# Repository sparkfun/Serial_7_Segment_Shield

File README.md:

Serial_7_Segment_Shield
=======================

The Serial 7 Segment Shield allows for easy use of the 4 digit 1" seven segment displays.

Repository Contents
-------------------

* **/hardware** - Eagle PCB layout files

Version History
---------------
* vH02 First production run
* vH01 First protoboard run.

License Information
-------------------

The hardware is released under [Creative Commons Share-alike 3.0](http://creativecommons.org/licenses/by-sa/3.0/).

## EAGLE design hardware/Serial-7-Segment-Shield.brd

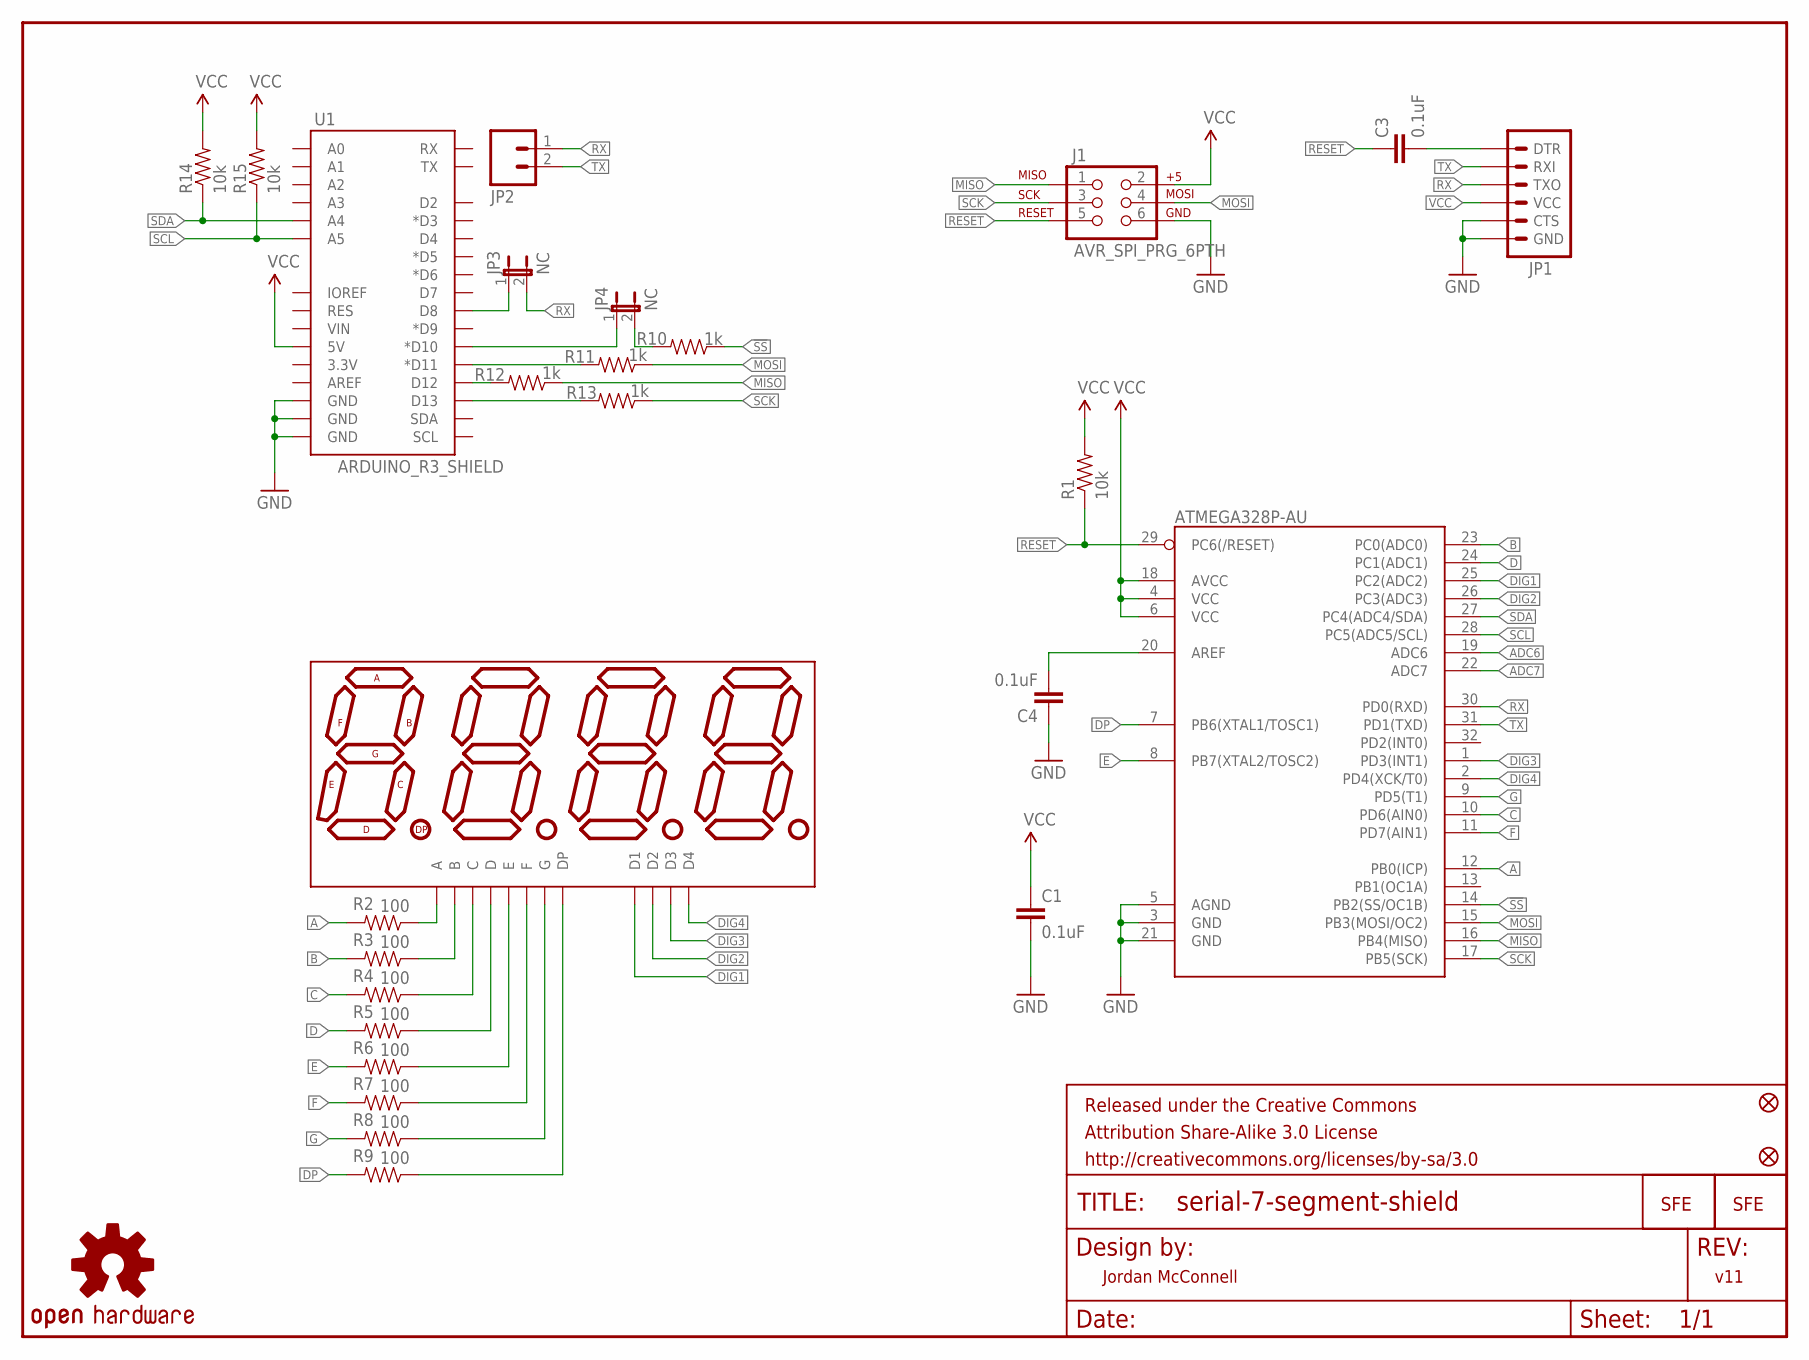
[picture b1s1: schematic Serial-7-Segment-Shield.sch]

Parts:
ATMEGA328P-AU: ATMEGA328P-AU; TQFP32-08
C1, C3, C4: 0.1uF; 0603-CAP
FID1, FID2: FIDUCIAL1X2; FIDUCIAL-1X2
FRAME1: FRAME-LETTER; CREATIVE_COMMONS
J1: AVR_SPI_PRG_6PTH; 2X3
JP1: ARDUINO_SERIAL_PROGRAMPTH; 1X06
JP2: M02PTH; 1X02
JP3, JP4: NC; SJ_2S
LOGO1, LOGO2: LOGO-SFENEW; SFE-NEW-WEBLOGO
R1, R14, R15: 10k; 0603-RES
R2, R3, R4, R5, R6, R7, R8, R9: 100; 0603-RES
R10, R11, R12, R13: 1k; 0603-RES
U1: ARDUINO_R3_SHIELD; UNO_R3_SHIELD
U$1: 7-SEGMENT-4DIGIT-COUNTERPTH; 7-SEGMENT-4DIGIT-COUNTER
U$4: OSHW-LOGOS; OSHW-LOGO-S

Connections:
!SS: ATMEGA328P-AU.14 (PB2(SS/OC1B)), R10.1
A: ATMEGA328P-AU.12 (PB0(ICP)), R2.2
ADC6: ATMEGA328P-AU.19 (ADC6)
ADC7: ATMEGA328P-AU.22 (ADC7)
B: ATMEGA328P-AU.23 (PC0(ADC0)), R3.2
C: ATMEGA328P-AU.10 (PD6(AIN0)), R4.2
D: ATMEGA328P-AU.24 (PC1(ADC1)), R5.2
DIG1: ATMEGA328P-AU.25 (PC2(ADC2)), U$1.12 (D1)
DIG2: ATMEGA328P-AU.26 (PC3(ADC3)), U$1.9 (D2)
DIG3: ATMEGA328P-AU.1 (PD3(INT1)), U$1.8 (D3)
DIG4: ATMEGA328P-AU.2 (PD4(XCK/T0)), U$1.6 (D4)
DP: ATMEGA328P-AU.7 (PB6(XTAL1/TOSC1)), R9.2
E: ATMEGA328P-AU.8 (PB7(XTAL2/TOSC2)), R6.2
F: ATMEGA328P-AU.11 (PD7(AIN1)), R7.2
G: ATMEGA328P-AU.9 (PD5(T1)), R8.2
GND: ATMEGA328P-AU.3 (GND), ATMEGA328P-AU.5 (AGND), ATMEGA328P-AU.21 (GND), C1.2, C4.1, J1.6, JP1.5 (CTS), JP1.6 (GND), U1.GND@0 (GND), U1.GND@1 (GND), U1.GND@2 (GND)
MISO: ATMEGA328P-AU.16 (PB4(MISO)), J1.1, R12.1
MOSI: ATMEGA328P-AU.15 (PB3(MOSI/OC2)), J1.4, R11.1
unnamed: ATMEGA328P-AU.20 (AREF), C4.2
unnamed: R13.2, U1.D13
unnamed: R12.2, U1.D12
unnamed: R11.2, U1.D11 (*D11)
unnamed: JP4.2, R10.2
unnamed: JP4.1, U1.D10 (*D10)
unnamed: JP3.1, U1.D8
unnamed: R2.1, U$1.11 (A)
unnamed: R3.1, U$1.7 (B)
unnamed: C3.2, JP1.1 (DTR)
unnamed: R4.1, U$1.4 (C)
unnamed: R5.1, U$1.2 (D)
unnamed: R6.1, U$1.1 (E)
unnamed: R7.1, U$1.10 (F)
unnamed: R8.1, U$1.5 (G)
unnamed: R9.1, U$1.3 (DP)
RESET: ATMEGA328P-AU.29 (PC6(/RESET)), C3.1, J1.5, R1.1
RX: ATMEGA328P-AU.30 (PD0(RXD)), JP1.3 (TXO), JP2.1, JP3.2
SCK: ATMEGA328P-AU.17 (PB5(SCK)), J1.3, R13.1
SCL: ATMEGA328P-AU.28 (PC5(ADC5/SCL)), R15.1, U1.A5
SDA: ATMEGA328P-AU.27 (PC4(ADC4/SDA)), R14.1, U1.A4
TX: ATMEGA328P-AU.31 (PD1(TXD)), JP1.2 (RXI), JP2.2
VCC: ATMEGA328P-AU.4 (VCC), ATMEGA328P-AU.6 (VCC), ATMEGA328P-AU.18 (AVCC), C1.1, J1.2, JP1.4 (VCC), R1.2, R14.2, R15.2, U1.5V

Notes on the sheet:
Jordan McConnell
v11

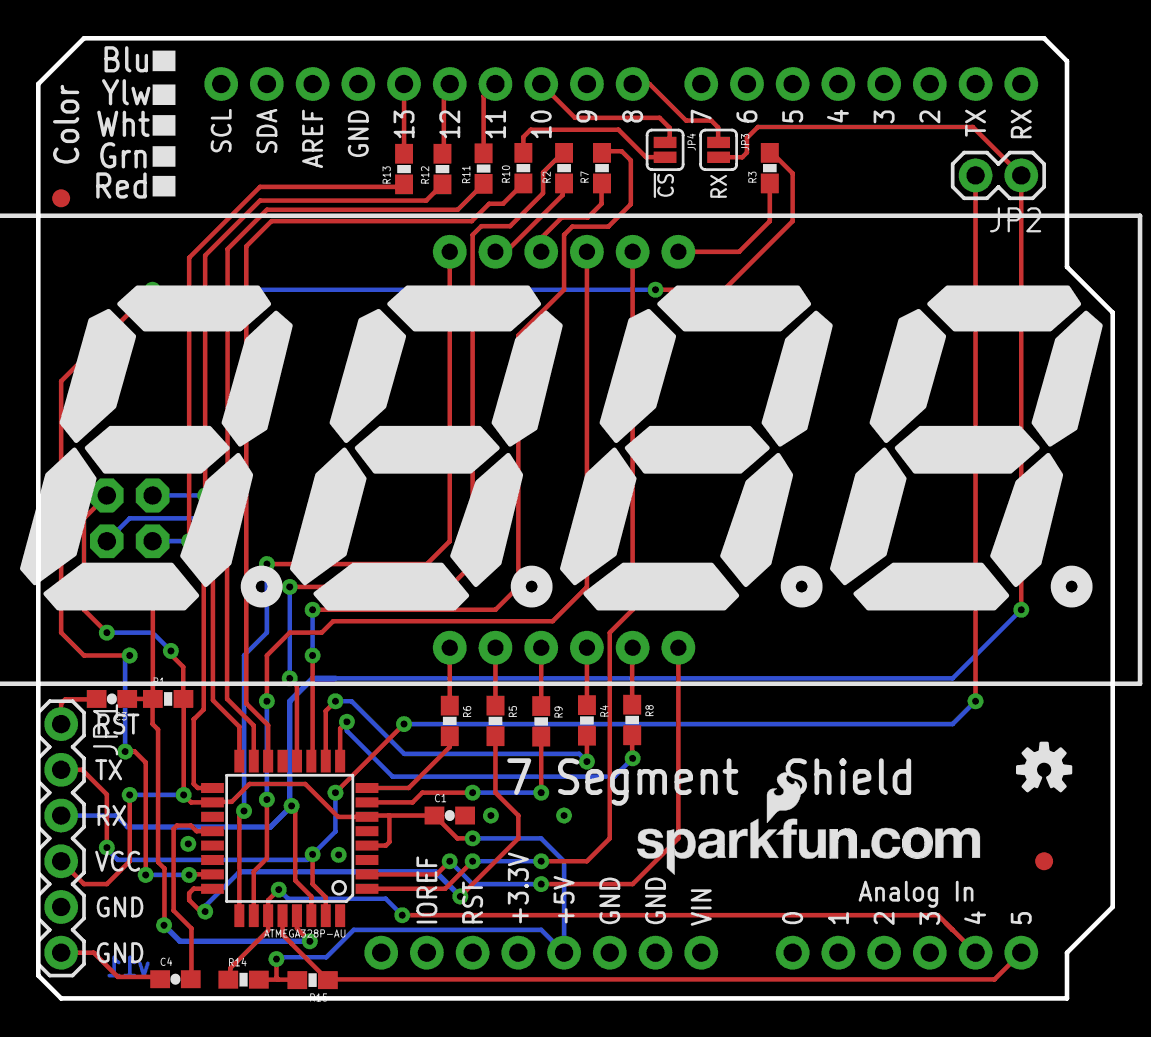
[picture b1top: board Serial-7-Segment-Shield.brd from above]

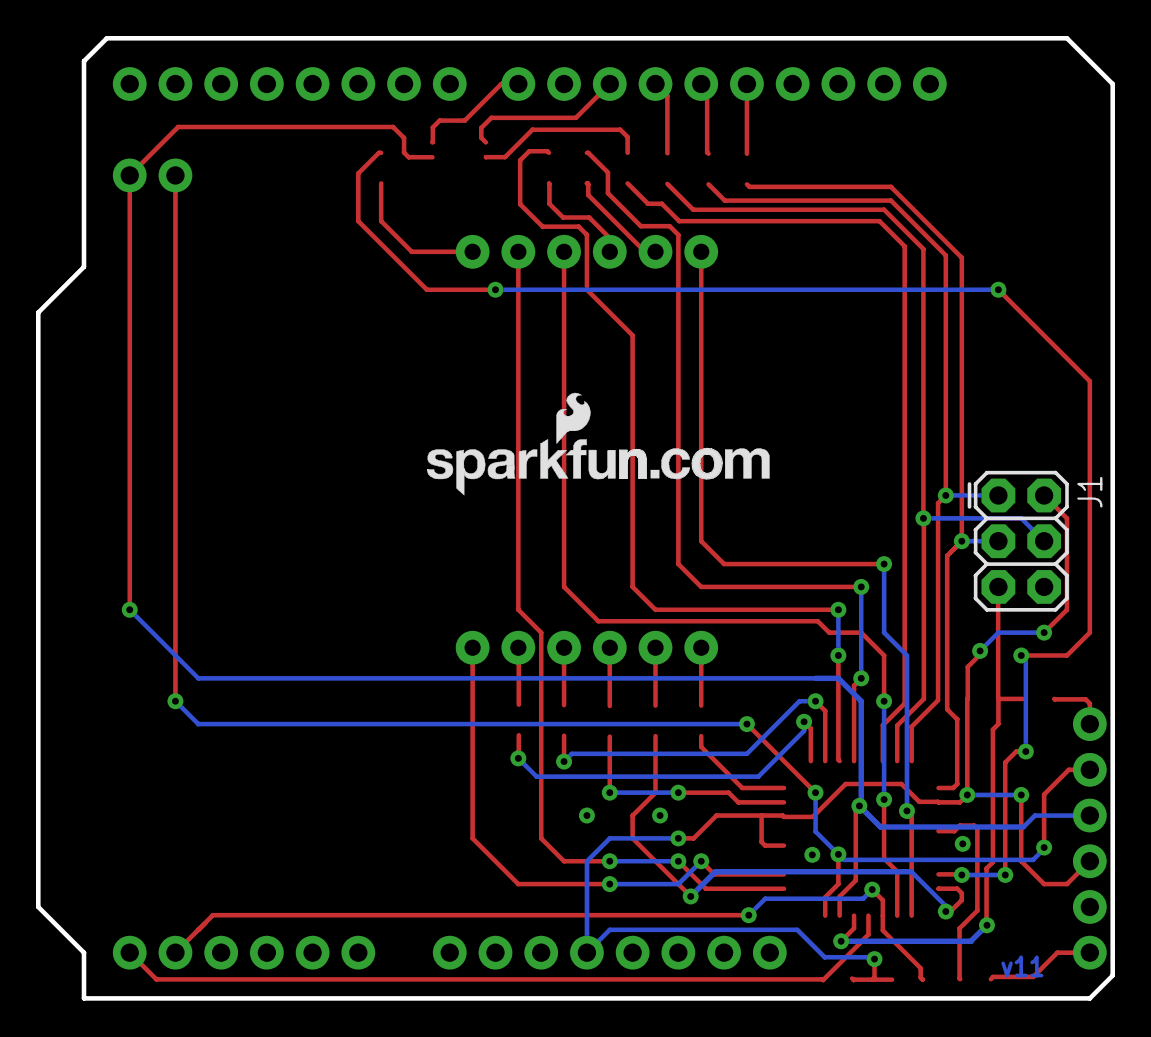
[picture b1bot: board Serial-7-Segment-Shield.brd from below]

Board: 2 copper layers, 59.7 x 53.3 mm, 32 parts (2 on the bottom side), 39 nets.

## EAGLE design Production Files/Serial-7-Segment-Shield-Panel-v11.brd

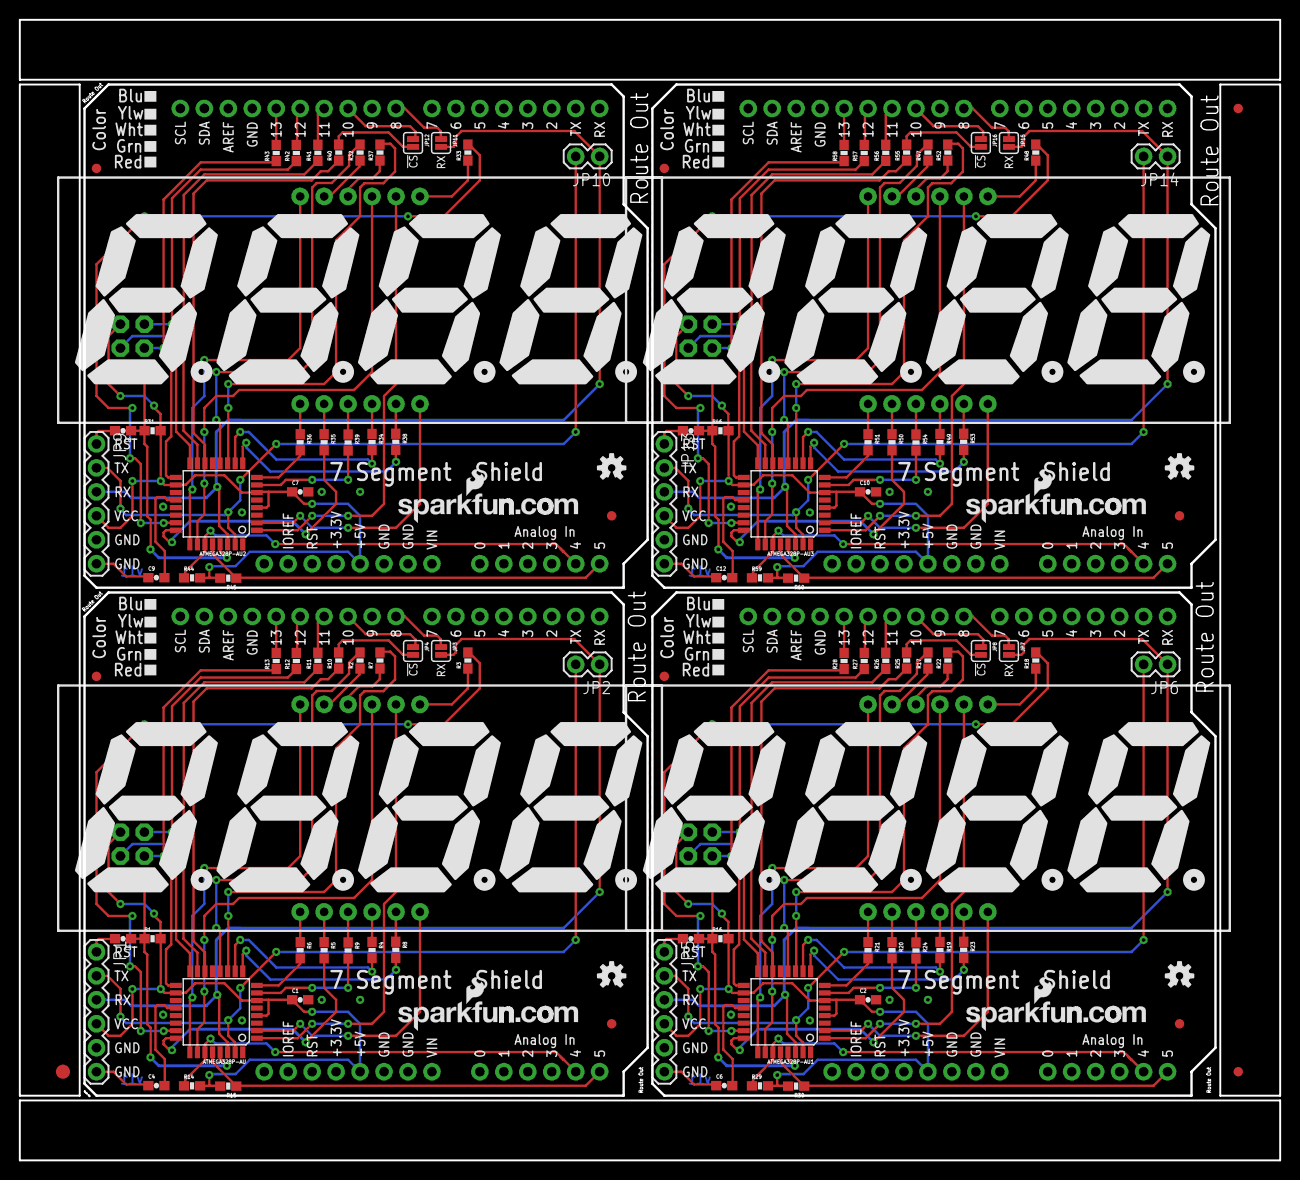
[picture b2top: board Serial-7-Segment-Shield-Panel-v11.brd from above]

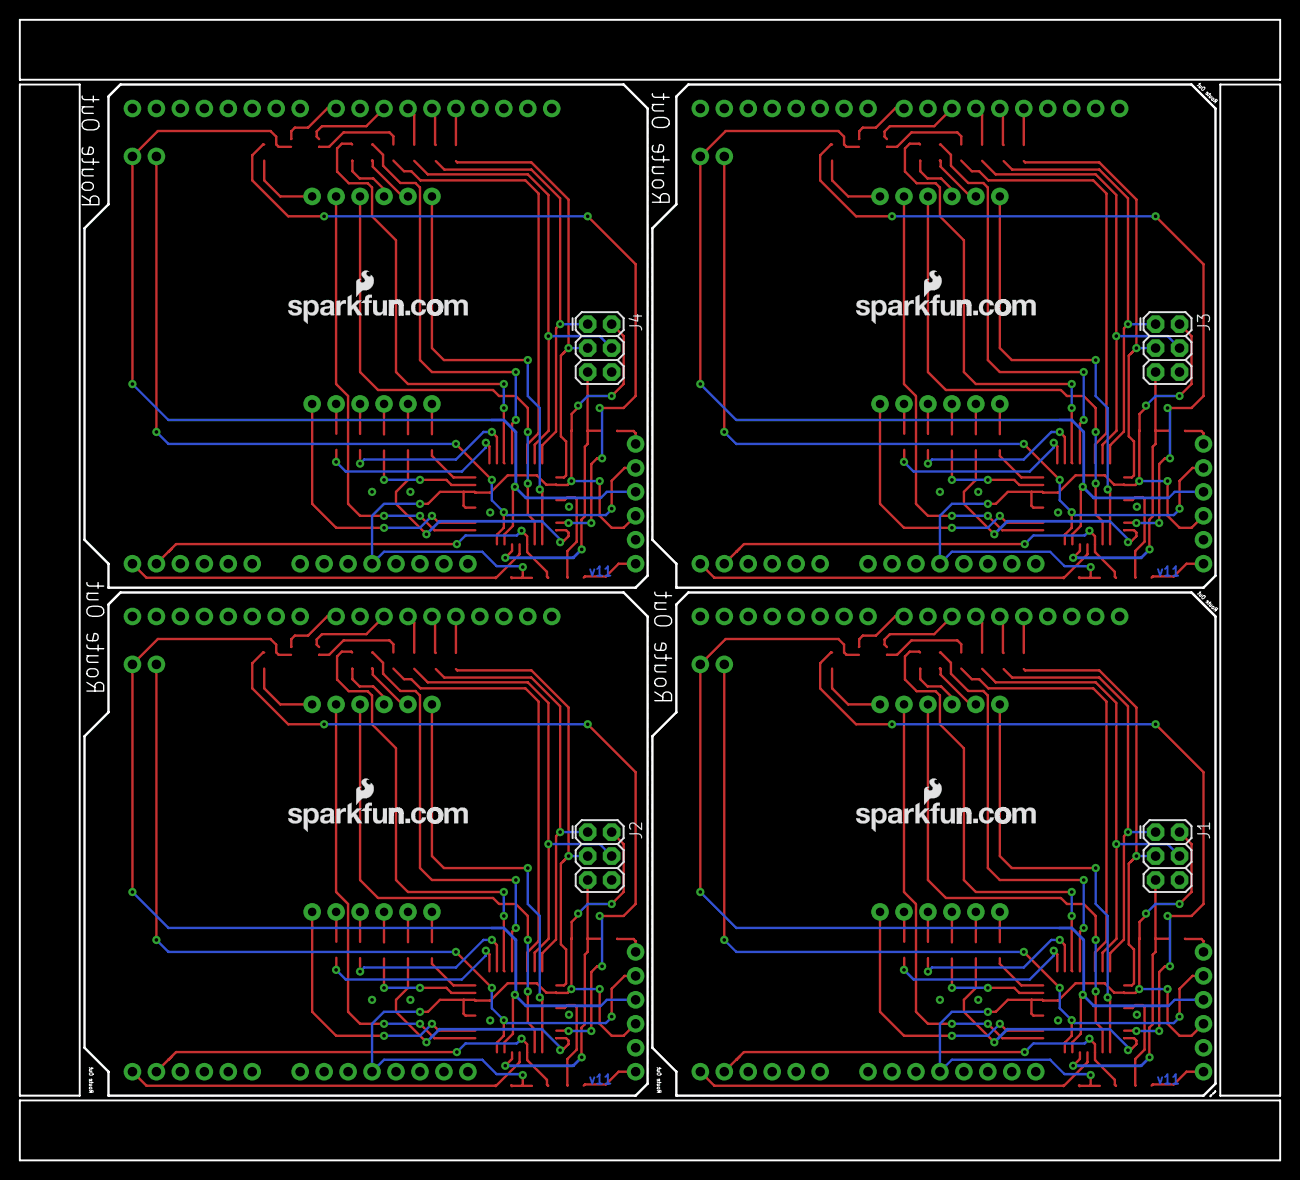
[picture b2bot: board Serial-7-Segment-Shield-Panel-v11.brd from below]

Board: 2 copper layers, 133.6 x 120.9 mm, 127 parts (8 on the bottom side), 156 nets.

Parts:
ATMEGA328P-AU, ATMEGA328P-AU1, ATMEGA328P-AU2, ATMEGA328P-AU3: ATMEGA328P-AU; TQFP32-08
C1, C2, C3, C4, C5, C6, C7, C8, C9, C10, C11, C12: 0.1uF; 0603-CAP
E$1: FIDUCIAL-1.5X3
E$4, E$5: FIDUCIAL-1X2
FID1, FID2, FID3, FID4, FID5, FID6, FID7, FID8: FIDUCIAL1X2; FIDUCIAL-1X2
J1, J2, J3, J4: AVR_SPI_PRG_6PTH; 2X3
JP1, JP5, JP9, JP13: 1X06
JP2, JP6, JP10, JP14: 1X02
JP3, JP4, JP7, JP8, JP11, JP12, JP15, JP16: NC; SJ_2S
LOGO1, LOGO2, LOGO3, LOGO4, LOGO5, LOGO6, LOGO7, LOGO8: LOGO-SFENEW; SFE-NEW-WEBLOGO
R1, R14, R15, R16, R29, R30, R31, R44, R45, R46, R59, R60: 10k; 0603-RES
R2, R3, R4, R5, R6, R7, R8, R9, R17, R18, R19, R20, R21, R22, R23, R24, R32, R33, R34, R35, R36, R37, R38, R39, R47, R48, R49, R50, R51, R52, R53, R54: 100; 0603-RES
R10, R11, R12, R13, R25, R26, R27, R28, R40, R41, R42, R43, R55, R56, R57, R58: 1k; 0603-RES
U1, U2, U3, U4: ARDUINO_R3_SHIELD; UNO_R3_SHIELD
U$1, U$3, U$6, U$8: 7-SEGMENT-4DIGIT-COUNTERPTH; 7-SEGMENT-4DIGIT-COUNTER
U$2, U$4, U$5, U$7: OSHW-LOGOS; OSHW-LOGO-S

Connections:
!SS: ATMEGA328P-AU.14, R10.1
!SS1: ATMEGA328P-AU1.14, R25.1
!SS2: ATMEGA328P-AU2.14, R40.1
!SS3: ATMEGA328P-AU3.14, R55.1
A: ATMEGA328P-AU.12, R2.2
A1: ATMEGA328P-AU1.12, R17.2
A2: ATMEGA328P-AU2.12, R32.2
A3: ATMEGA328P-AU3.12, R47.2
B: ATMEGA328P-AU.23, R3.2
B1: ATMEGA328P-AU1.23, R18.2
B2: ATMEGA328P-AU2.23, R33.2
B3: ATMEGA328P-AU3.23, R48.2
C: ATMEGA328P-AU.10, R4.2
C1: ATMEGA328P-AU1.10, R19.2
C2: ATMEGA328P-AU2.10, R34.2
C3: ATMEGA328P-AU3.10, R49.2
D: ATMEGA328P-AU.24, R5.2
D1: ATMEGA328P-AU1.24, R20.2
D2: ATMEGA328P-AU2.24, R35.2
D3: ATMEGA328P-AU3.24, R50.2
DIG1: ATMEGA328P-AU.25, U$1.12
DIG2: ATMEGA328P-AU.26, U$1.9
DIG3: ATMEGA328P-AU.1, U$1.8
DIG4: ATMEGA328P-AU.2, U$1.6
DIG5: ATMEGA328P-AU1.2, U$3.6
DIG6: ATMEGA328P-AU1.1, U$3.8
DIG7: ATMEGA328P-AU1.26, U$3.9
DIG8: ATMEGA328P-AU1.25, U$3.12
DIG9: ATMEGA328P-AU2.2, U$6.6
DIG10: ATMEGA328P-AU2.1, U$6.8
DIG11: ATMEGA328P-AU2.26, U$6.9
DIG12: ATMEGA328P-AU2.25, U$6.12
DIG13: ATMEGA328P-AU3.2, U$8.6
DIG14: ATMEGA328P-AU3.1, U$8.8
DIG15: ATMEGA328P-AU3.26, U$8.9
DIG16: ATMEGA328P-AU3.25, U$8.12
DP: ATMEGA328P-AU.7, R9.2
DP1: ATMEGA328P-AU1.7, R24.2
DP2: ATMEGA328P-AU2.7, R39.2
DP3: ATMEGA328P-AU3.7, R54.2
E: ATMEGA328P-AU.8, R6.2
E1: ATMEGA328P-AU1.8, R21.2
E2: ATMEGA328P-AU2.8, R36.2
E3: ATMEGA328P-AU3.8, R51.2
F: ATMEGA328P-AU.11, R7.2
F1: ATMEGA328P-AU1.11, R22.2
F2: ATMEGA328P-AU2.11, R37.2
F3: ATMEGA328P-AU3.11, R52.2
G: ATMEGA328P-AU.9, R8.2
G1: ATMEGA328P-AU1.9, R23.2
G2: ATMEGA328P-AU2.9, R38.2
G3: ATMEGA328P-AU3.9, R53.2
GND: ATMEGA328P-AU.3, ATMEGA328P-AU.5, ATMEGA328P-AU.21, C1.2, C4.1, J1.6, JP1.5, JP1.6, U1.GND@0, U1.GND@1, U1.GND@2
GND1: ATMEGA328P-AU1.3, ATMEGA328P-AU1.5, ATMEGA328P-AU1.21, C2.2, C6.1, J2.6, JP5.5, JP5.6, U2.GND@0, U2.GND@1, U2.GND@2
GND2: ATMEGA328P-AU2.3, ATMEGA328P-AU2.5, ATMEGA328P-AU2.21, C7.2, C9.1, J3.6, JP9.5, JP9.6, U3.GND@0, U3.GND@1, U3.GND@2
GND3: ATMEGA328P-AU3.3, ATMEGA328P-AU3.5, ATMEGA328P-AU3.21, C10.2, C12.1, J4.6, JP13.5, JP13.6, U4.GND@0, U4.GND@1, U4.GND@2
MISO: ATMEGA328P-AU.16, J1.1, R12.1
MISO1: ATMEGA328P-AU1.16, J2.1, R27.1
MISO2: ATMEGA328P-AU2.16, J3.1, R42.1
MISO3: ATMEGA328P-AU3.16, J4.1, R57.1
MOSI: ATMEGA328P-AU.15, J1.4, R11.1
MOSI1: ATMEGA328P-AU1.15, J2.4, R26.1
MOSI2: ATMEGA328P-AU2.15, J3.4, R41.1
MOSI3: ATMEGA328P-AU3.15, J4.4, R56.1
unnamed: ATMEGA328P-AU.20, C4.2
unnamed: R13.2, U1.D13
unnamed: R12.2, U1.D12
unnamed: R11.2, U1.D11
unnamed: JP4.2, R10.2
unnamed: JP4.1, U1.D10
unnamed: JP3.1, U1.D8
unnamed: C5.2, JP5.1
unnamed: ATMEGA328P-AU1.20, C6.2
unnamed: R17.1, U$3.11
unnamed: R2.1, U$1.11
unnamed: R3.1, U$1.7
unnamed: C3.2, JP1.1
unnamed: R4.1, U$1.4
unnamed: R5.1, U$1.2
unnamed: R6.1, U$1.1
unnamed: R7.1, U$1.10
unnamed: R8.1, U$1.5
unnamed: R9.1, U$1.3
unnamed: R18.1, U$3.7
unnamed: R19.1, U$3.4
unnamed: R20.1, U$3.2
unnamed: R21.1, U$3.1
unnamed: R22.1, U$3.10
unnamed: R23.1, U$3.5
unnamed: R24.1, U$3.3
unnamed: R28.2, U2.D13
unnamed: R27.2, U2.D12
unnamed: R26.2, U2.D11
unnamed: JP8.2, R25.2
unnamed: JP8.1, U2.D10
unnamed: JP7.1, U2.D8
unnamed: C8.2, JP9.1
unnamed: ATMEGA328P-AU2.20, C9.2
unnamed: R32.1, U$6.11
unnamed: R33.1, U$6.7
unnamed: R34.1, U$6.4
unnamed: R35.1, U$6.2
unnamed: R36.1, U$6.1
unnamed: R37.1, U$6.10
unnamed: R38.1, U$6.5
unnamed: R39.1, U$6.3
unnamed: R43.2, U3.D13
unnamed: R42.2, U3.D12
unnamed: R41.2, U3.D11
unnamed: JP12.2, R40.2
unnamed: JP12.1, U3.D10
unnamed: JP11.1, U3.D8
unnamed: C11.2, JP13.1
unnamed: ATMEGA328P-AU3.20, C12.2
unnamed: R47.1, U$8.11
unnamed: R48.1, U$8.7
unnamed: R49.1, U$8.4
unnamed: R50.1, U$8.2
unnamed: R51.1, U$8.1
unnamed: R52.1, U$8.10
unnamed: R53.1, U$8.5
unnamed: R54.1, U$8.3
unnamed: R58.2, U4.D13
unnamed: R57.2, U4.D12
unnamed: R56.2, U4.D11
unnamed: JP16.2, R55.2
unnamed: JP16.1, U4.D10
unnamed: JP15.1, U4.D8
RESET: ATMEGA328P-AU.29, C3.1, J1.5, R1.1
RESET1: ATMEGA328P-AU1.29, C5.1, J2.5, R16.1
RESET2: ATMEGA328P-AU2.29, C8.1, J3.5, R31.1
RESET3: ATMEGA328P-AU3.29, C11.1, J4.5, R46.1
RX: ATMEGA328P-AU.30, JP1.3, JP2.1, JP3.2
RX1: ATMEGA328P-AU1.30, JP5.3, JP6.1, JP7.2
RX2: ATMEGA328P-AU2.30, JP9.3, JP10.1, JP11.2
RX3: ATMEGA328P-AU3.30, JP13.3, JP14.1, JP15.2
SCK: ATMEGA328P-AU.17, J1.3, R13.1
SCK1: ATMEGA328P-AU1.17, J2.3, R28.1
SCK2: ATMEGA328P-AU2.17, J3.3, R43.1
SCK3: ATMEGA328P-AU3.17, J4.3, R58.1
SCL: ATMEGA328P-AU.28, R15.1, U1.A5
SCL1: ATMEGA328P-AU1.28, R30.1, U2.A5
SCL2: ATMEGA328P-AU2.28, R45.1, U3.A5
SCL3: ATMEGA328P-AU3.28, R60.1, U4.A5
SDA: ATMEGA328P-AU.27, R14.1, U1.A4
SDA1: ATMEGA328P-AU1.27, R29.1, U2.A4
SDA2: ATMEGA328P-AU2.27, R44.1, U3.A4
SDA3: ATMEGA328P-AU3.27, R59.1, U4.A4
TX: ATMEGA328P-AU.31, JP1.2, JP2.2
TX1: ATMEGA328P-AU1.31, JP5.2, JP6.2
TX2: ATMEGA328P-AU2.31, JP9.2, JP10.2
TX3: ATMEGA328P-AU3.31, JP13.2, JP14.2
VCC: ATMEGA328P-AU.4, ATMEGA328P-AU.6, ATMEGA328P-AU.18, C1.1, J1.2, JP1.4, R1.2, R14.2, R15.2, U1.5V
VCC1: ATMEGA328P-AU1.4, ATMEGA328P-AU1.6, ATMEGA328P-AU1.18, C2.1, J2.2, JP5.4, R16.2, R29.2, R30.2, U2.5V
VCC2: ATMEGA328P-AU2.4, ATMEGA328P-AU2.6, ATMEGA328P-AU2.18, C7.1, J3.2, JP9.4, R31.2, R44.2, R45.2, U3.5V
VCC3: ATMEGA328P-AU3.4, ATMEGA328P-AU3.6, ATMEGA328P-AU3.18, C10.1, J4.2, JP13.4, R46.2, R59.2, R60.2, U4.5V

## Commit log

2013-03-15 Added v01 hardware
2013-03-15 Added more info to the readme.
2013-05-03 Updated hardware to v02.
2013-05-06 Minor update to v02, now includes color selection silk.
2013-05-06 v10 Production Ready files
    Change version number on boards to v10
    Created board panel for manufacture
2013-10-18 0603 Cap/Res Change
    Changed all caps and res to 0603, minor trace re-routing
2013-10-18 Trace width and drill size updates
    Standardized trace width to 8mil. Standardized drill size to 15mil.
2014-03-10 commit to QC branch
2014-03-11 DESK CHANGE
2014-03-13 Trace re-routes
2014-04-05 changed micro fid to regular
2014-04-05 created v11 panel

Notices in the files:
parts and their libraries:
SparkFun-Aesthetics: Licensing: CC v3.0 Share-Alike You are welcome to use this library for commercial purposes.
SparkFun-Retired: Licensing:Creative Commons ShareAlike 4.0 International - https://creativecommons.org/licenses/by-sa/4.0
SparkFun-Aesthetics: Released under the Creative Commons
